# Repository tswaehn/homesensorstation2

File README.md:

# homesensorstation2

## requirements
*  NodeMCU Board
   * Arduino compatible ESP8266 controller board (4MB flash, I2C, SPI, WiFi, ... )
   * doc in german https://www.mikrocontroller-elektronik.de/nodemcu-esp8266-tutorial-wlan-board-arduino-ide/
*  RFM12B
   * https://www.ebay.de/itm/RFM12B-868Mhz-Wireless-Transceiver-from-HopeRF-RFM12B-868S2P-/171670876052
*  HomeSensor2 Base board
   * this board hosts the RFM12B, SSD1306 display and NodeMCU
   * schematics is in the repo 
*  SSD1306 display (128x64 pixels)
   * any compatible display with I2C will do
*  Sensors must be TX29 compatible
   * see here http://fredboboss.free.fr/articles/tx29.php
*  Arduino IDE 1.8.9
   * I personally prefer exactly this version, others may do it as well

## installation
*  install ESP8266 boards (follow instructions https://github.com/esp8266/Arduino)
*  load the arduino project
*  select "Tools" - "Board" - "NodeMCU (ESP 12E Module)" 
*  select "Tools" - "Port" 
*  run compile button in Arduino
*  upload to NodeMCU
*  done

***ATTENTION !!!!***

* use ardino IDE version 1.8.5
* use ESP library https://arduino.esp8266.com/stable/package_esp8266com_index.json
* use EPS board version 2.7.4
* use settings:
   * arduino_esp_settings.png

## pin-out
*  SSD1306 Display 
   * SDA: D2
   * SCL: D1
*  RFM12B
   * MOSI: D7
   * MISO: D6
   * SCK: D5
   * SS: D8
   * IRQ: D0

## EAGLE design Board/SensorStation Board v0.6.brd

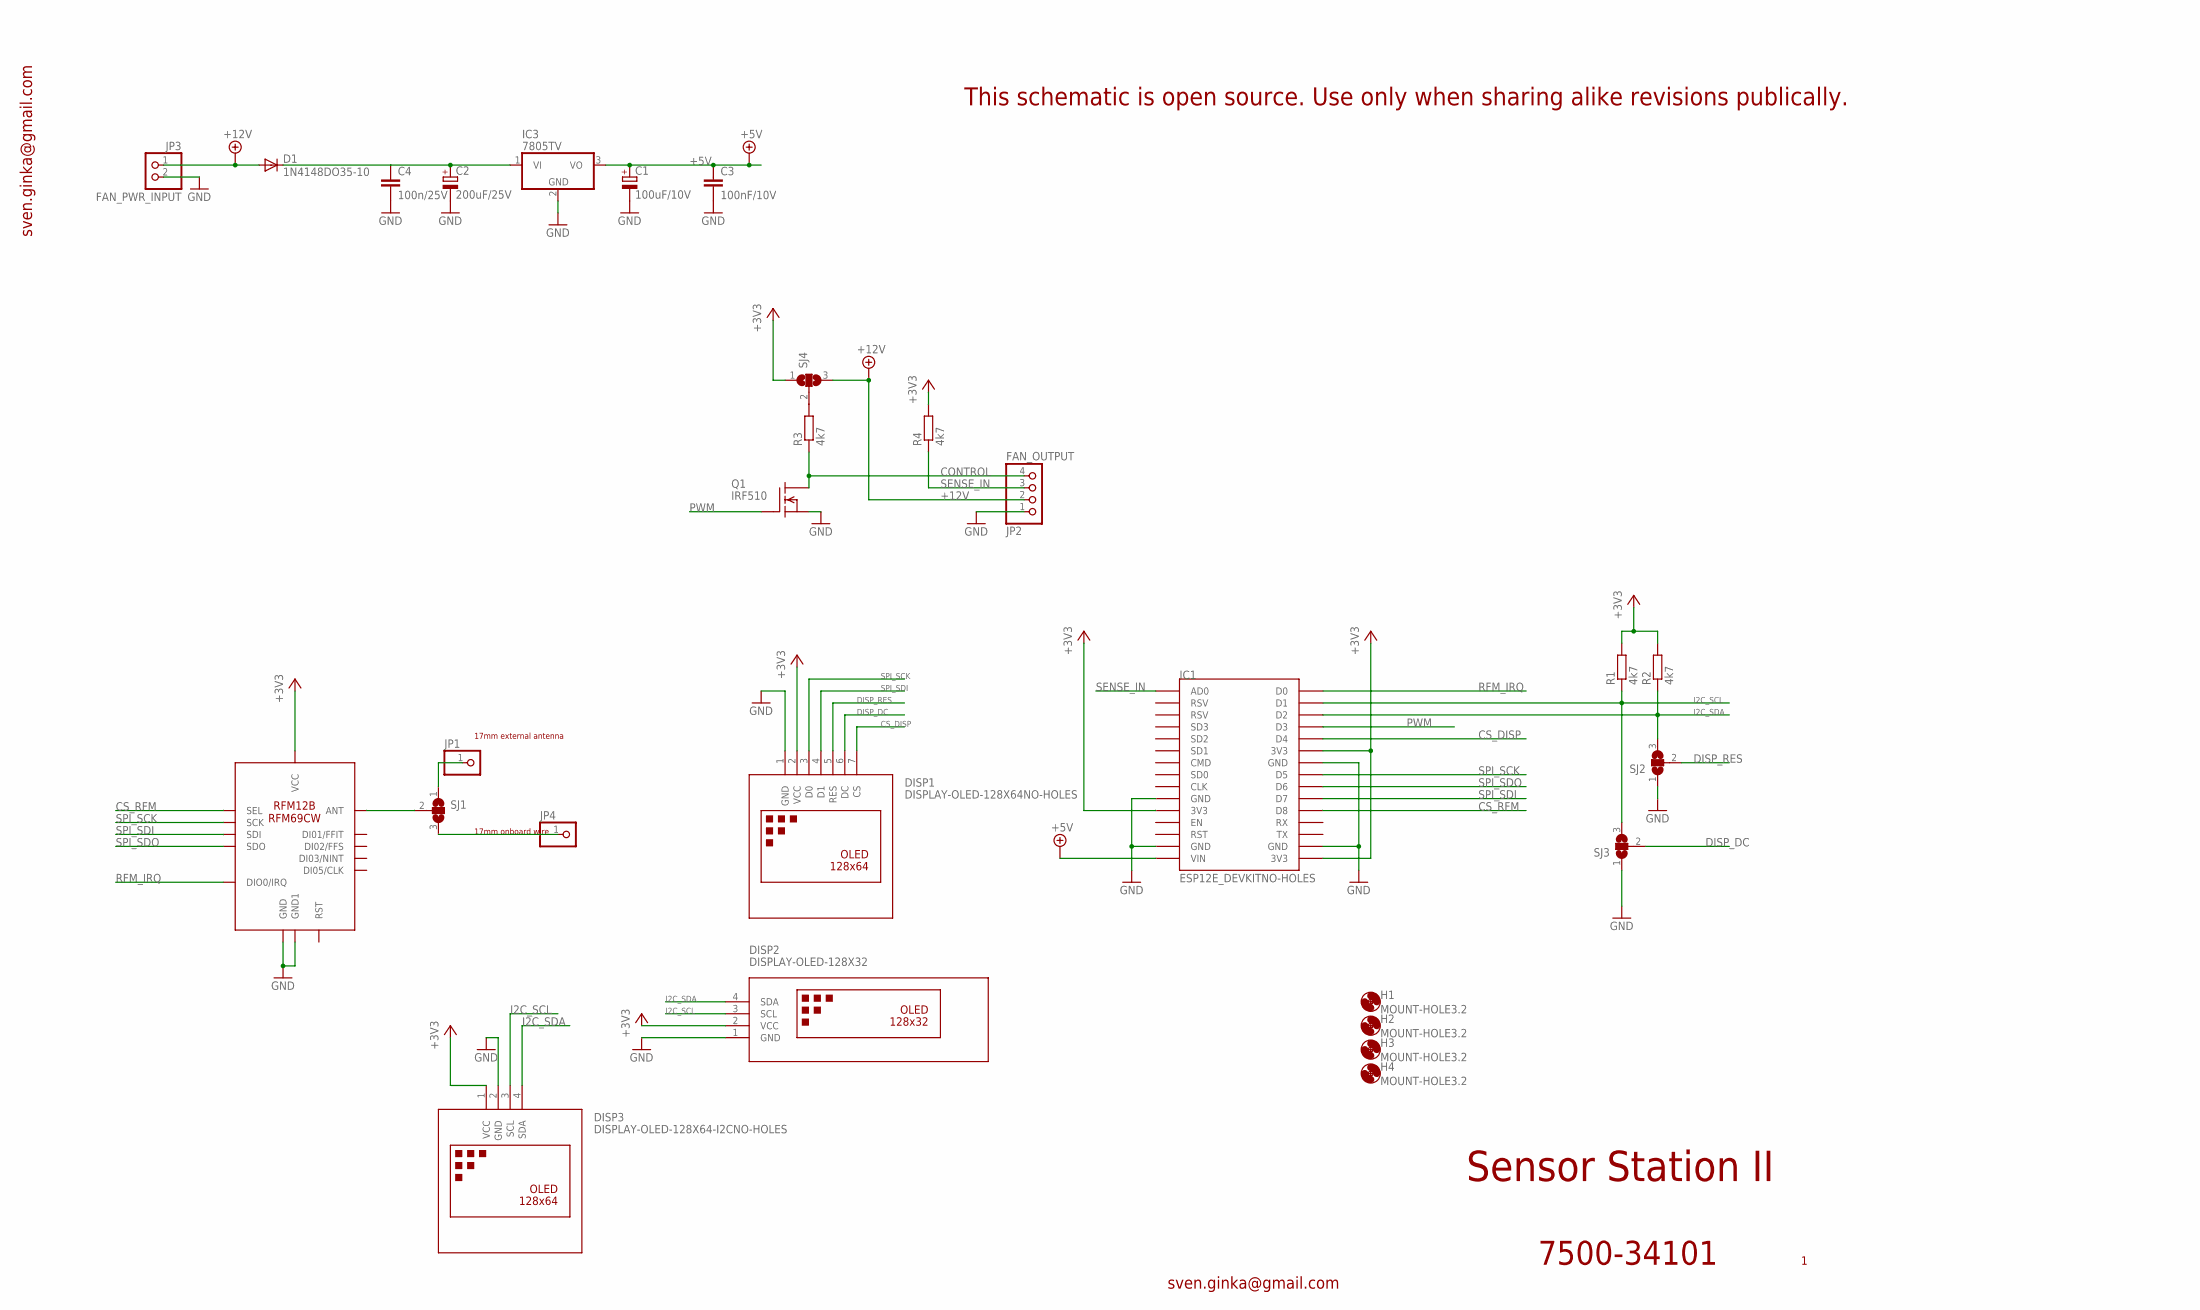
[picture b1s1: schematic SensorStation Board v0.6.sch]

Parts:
C1: 100uF/10V; E2,5-6
C2: 200uF/25V; E2,5-6
C3: 100nF/10V; C025-025X050
C4: 100n/25V; C025-025X050
D1: 1N4148DO35-10; DO35-10
DISP1: DISPLAY-OLED-128X64NO-HOLES; DISPLAY-OLED-128X64-NO-HOLES
DISP2: DISPLAY-OLED-128X32
DISP3: DISPLAY-OLED-128X64-I2CNO-HOLES; DISPLAY-OLED-128X64-I2C-NO-HOLES
H1, H2, H3, H4: MOUNT-HOLE3.2; 3,2
IC1: ESP12E_DEVKITNO-HOLES; ESP12E_DEVKIT-NO-HOLES
IC2: RFM12B/69CW
IC3: 7805TV; TO220V
JP1, JP4: PINHD-1X1; 1X01
JP2: FAN_OUTPUT; 1X04
JP3: FAN_PWR_INPUT; 1X02
Q1: IRF510; TO220
R1, R2, R3, R4: 4k7; 0204/5
SJ1, SJ2, SJ3, SJ4: SJ2W; SJ_2

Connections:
12V_INTERNAL: C2.+, C4.1, D1.C, IC3.1 (VI)
+3V3: DISP1.2 (VCC), DISP2.2 (VCC), DISP3.1 (VCC), IC1.3V3@0 (3V3), IC1.3V3@1 (3V3), IC1.3V3@2 (3V3), IC2.VDD (VCC), R1.2, R2.2, R4.2, SJ4.1
+5V: C1.+, C3.1, IC1.VIN, IC3.3 (VO)
+12V: D1.A, JP2.2, JP3.1, SJ4.3
ANTENNA: JP4.1, SJ1.3
CONTROL: JP2.4, Q1.2 (D), R3.1
CS_DISP: DISP1.7 (CS), IC1.D4
CS_RFM: IC1.D8, IC2.SEL
DISP_DC: DISP1.6 (DC), SJ3.2
DISP_RES: DISP1.5 (RES), SJ2.2
EXT_ANTENNA: JP1.1, SJ1.1
GND: C1.-, C2.-, C3.2, C4.2, DISP1.1 (GND), DISP2.1 (GND), DISP3.2 (GND), IC1.GND@0 (GND), IC1.GND@1 (GND), IC1.GND@2 (GND), IC1.GND@3 (GND), IC2.GND, IC2.GND1, IC3.2 (GND), JP2.1, JP3.2, Q1.3 (S), SJ2.1, SJ3.1
I2C_SCL: DISP2.3 (SCL), DISP3.3 (SCL), IC1.D1, R1.1, SJ3.3
I2C_SDA: DISP2.4 (SDA), DISP3.4 (SDA), IC1.D2, R2.1, SJ2.3
unnamed: IC2.ANT, SJ1.2
unnamed: R3.2, SJ4.2
PWM: IC1.D3, Q1.1 (G)
RFM_IRQ: IC1.D0, IC2.IRQ (DIO0/IRQ)
SENSE_IN: IC1.AD0, JP2.3, R4.1
SPI_SCK: DISP1.3 (D0), IC1.D5, IC2.SCK
SPI_SDI: DISP1.4 (D1), IC1.D7, IC2.SDI
SPI_SDO: IC1.D6, IC2.SDO

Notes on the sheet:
17mm onboard wire
17mm external antenna
Sensor Station II
sven.ginka@gmail.com
7500-34101
This schematic is open source. Use only when sharing alike revisions publically.

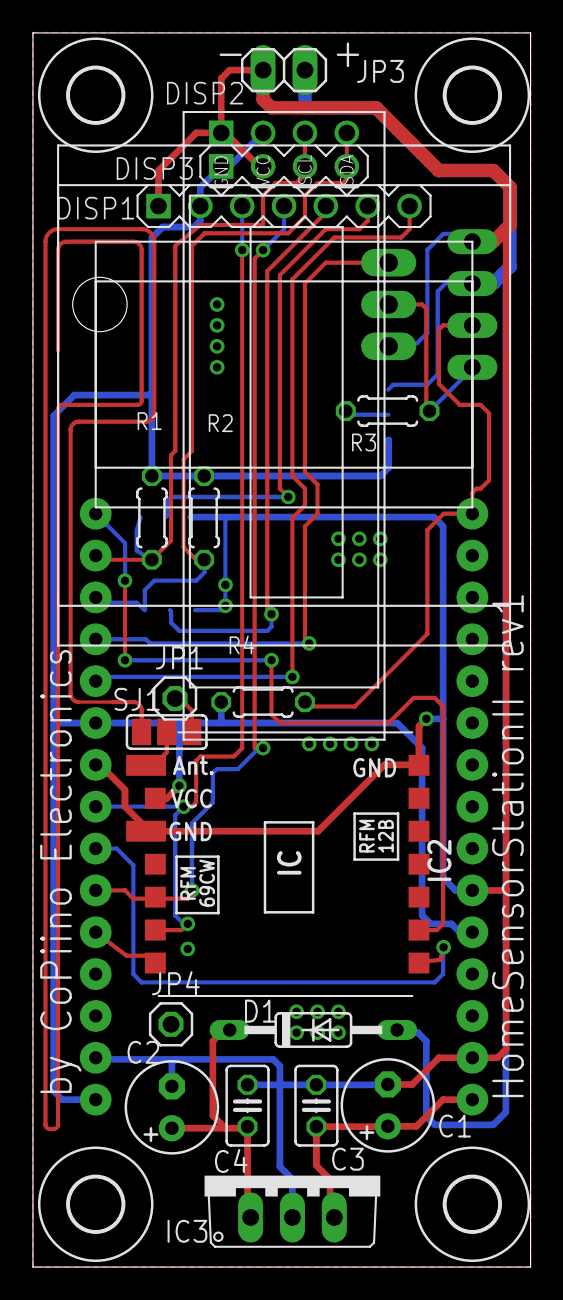
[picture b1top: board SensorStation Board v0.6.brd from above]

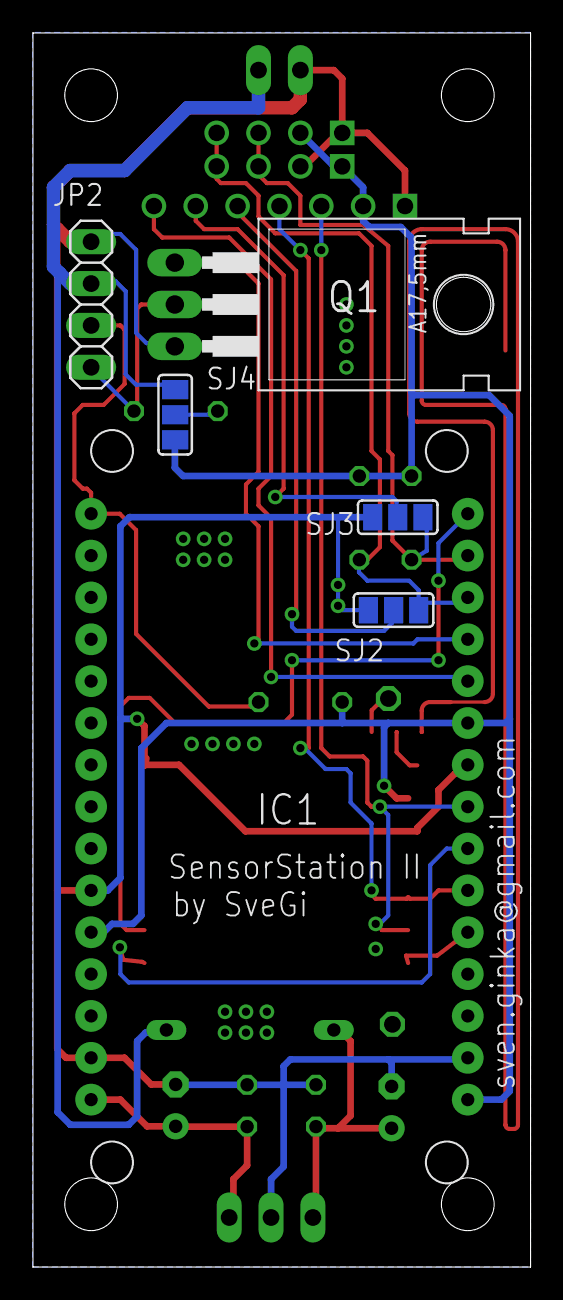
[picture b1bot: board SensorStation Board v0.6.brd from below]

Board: 2 copper layers, 30.2 x 74.9 mm, 28 parts (6 on the bottom side), 22 nets.

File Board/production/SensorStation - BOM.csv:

"Part";"Value";"Device";"Package";"Description";"";
"C1";"100uF/10V";"CPOL-EUE2.5-6";"E2,5-6";"POLARIZED CAPACITOR, European symbol";"";
"C2";"200uF/25V";"CPOL-EUE2.5-6";"E2,5-6";"POLARIZED CAPACITOR, European symbol";"";
"C3";"100nF/10V";"C-EU025-025X050";"C025-025X050";"CAPACITOR, European symbol";"";
"C4";"100n/25V";"C-EU025-025X050";"C025-025X050";"CAPACITOR, European symbol";"";
"D1";"1N4148DO35-10";"1N4148DO35-10";"DO35-10";"DIODE";"";
"DISP1";"DISPLAY-OLED-128X64NO-HOLES";"DISPLAY-OLED-128X64NO-HOLES";"DISPLAY-OLED-128X64-NO-HOLES";"128x64 Dot Matrix OLED Module";"";
"DISP2";"DISPLAY-OLED-128X32";"DISPLAY-OLED-128X32";"DISPLAY-OLED-128X32";"128x32 Dot Matrix OLED Module with I2C interface based on SSD1306 chip";"";
"DISP3";"DISPLAY-OLED-128X64-I2CNO-HOLES";"DISPLAY-OLED-128X64-I2CNO-HOLES";"DISPLAY-OLED-128X64-I2C-NO-HOLES";"OLED 0.96" 128x64 I2C Display";"";
"H1";"MOUNT-HOLE3.2";"MOUNT-HOLE3.2";"3,2";"MOUNTING HOLE with drill center marker";"";
"H2";"MOUNT-HOLE3.2";"MOUNT-HOLE3.2";"3,2";"MOUNTING HOLE with drill center marker";"";
"H3";"MOUNT-HOLE3.2";"MOUNT-HOLE3.2";"3,2";"MOUNTING HOLE with drill center marker";"";
"H4";"MOUNT-HOLE3.2";"MOUNT-HOLE3.2";"3,2";"MOUNTING HOLE with drill center marker";"";
"IC1";"ESP12E_DEVKITNO-HOLES";"ESP12E_DEVKITNO-HOLES";"ESP12E_DEVKIT-NO-HOLES";"ESP12E DEVKIT BOARD";"";
"IC2";"RFM12B/69CW";"RFM12B/69CW";"RFM12B/69CW";"";"";
"IC3";"7805TV";"7805TV";"TO220V";"Positive VOLTAGE REGULATOR";"";
"JP1";"";"PINHD-1X1";"1X01";"PIN HEADER";"";
"JP2";"FAN_OUTPUT";"PINHD-1X4";"1X04";"PIN HEADER";"";
"JP3";"FAN_PWR_INPUT";"PINHD-1X2";"1X02";"PIN HEADER";"";
"JP4";"";"PINHD-1X1";"1X01";"PIN HEADER";"";
"Q1";"IRF510";"IRF510";"TO220";"N-Channel Enhancement MOSFET (HEXFET); 100V; 5,6A; 0,54Ohm";"";
"R1";"4k7";"R-EU_0204/5";"0204/5";"RESISTOR, European symbol";"";
"R2";"4k7";"R-EU_0204/5";"0204/5";"RESISTOR, European symbol";"";
"R3";"4k7";"R-EU_0204/5";"0204/5";"RESISTOR, European symbol";"";
"R4";"4k7";"R-EU_0204/5";"0204/5";"RESISTOR, European symbol";"";
"SJ1";"";"SJ2W";"SJ_2";"SMD solder JUMPER";"";
"SJ2";"";"SJ2W";"SJ_2";"SMD solder JUMPER";"";
"SJ3";"";"SJ2W";"SJ_2";"SMD solder JUMPER";"";
"SJ4";"";"SJ2W";"SJ_2";"SMD solder JUMPER";"";

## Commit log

2020-08-23 mod: moved to dok and lbr
2020-08-23 mod: insert dok + lbr
2020-08-23 add: production data
2020-08-23 mod: moved JOB file to production
2020-08-23 add: pdf doks
2020-08-23 add: BOM
2020-08-29 add: arduino sources
2020-08-30 mod: re-org
2020-08-30 v2.3
2021-05-23 fix: startup + sensors IDs + warning notes on arduino IDE version + esp-board version

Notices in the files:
parts and their libraries:
diy-modules: Released under the Creative Commons Attribution 4.0 International License: http://creativecommons.org/licenses/by/4.0
